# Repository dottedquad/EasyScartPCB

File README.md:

# EasyScartPCB
A simplified SCART cable PCB optimized for US modded TVs and hand soldering

### Summary
This is a fork of [screwbreaker/ScartPCB](https://github.com/screwbreaker/ScartPCB) designed for SCART modding on US-market TVs. Since these TVs don't use the +12V auto-switch or aspect ratio signal (SCART pin 8), this design removes the unnecessary boost converter and optimizes for easier hand assembly and part sourcing.

### Key Improvements
- **Hand-solder friendly**: All 0805 components (no tiny 0402 parts)
- **Better component sourcing**: Single package "B" tantalum 220µF/6.3V for decoupling instead of multiple MLCCs
- **Simplified buffer**: Single 74LVC1G17 instead of two transistors
- **Complete grounding**: All SCART ground signals properly connected
- **Removes unnecessary boost converter**: US TVs don't need the +12V signal

### How It Works
The PCB is modular – use 0Ω resistors as jumpers to enable/disable signals as needed:

**CSYNC Buffer**: The 74LVC1G17 buffer is specifically for Genesis/Mega Drive systems. Genesis outputs a TTL-level CSYNC that loses voltage when loaded by the 470Ω series resistor and 75Ω termination resistor. The buffer maintains +5V for proper sync detection. Close the NOBUF jumper to bypass if not needed.

**RGB Signals**: Use 0Ω resistors to pass through or add 75Ω termination resistors as needed.

**Jumpers**: NOBUF (bypass CSYNC buffer), MONO (mix left/right audio), RGB (enable blanking signal).

### PCB Details
4-layer board designed to fit inside standard SCART connectors. All components are 0805 or larger for easy hand soldering.

### 3D-Printed Cable Gland
SCART connector cable glands are notoriously brittle, so this project includes a 3D-printed replacement that's more durable.

### License
The PCBs are under the CERN OHL license. This is an open project – improvements and contributions are welcome.

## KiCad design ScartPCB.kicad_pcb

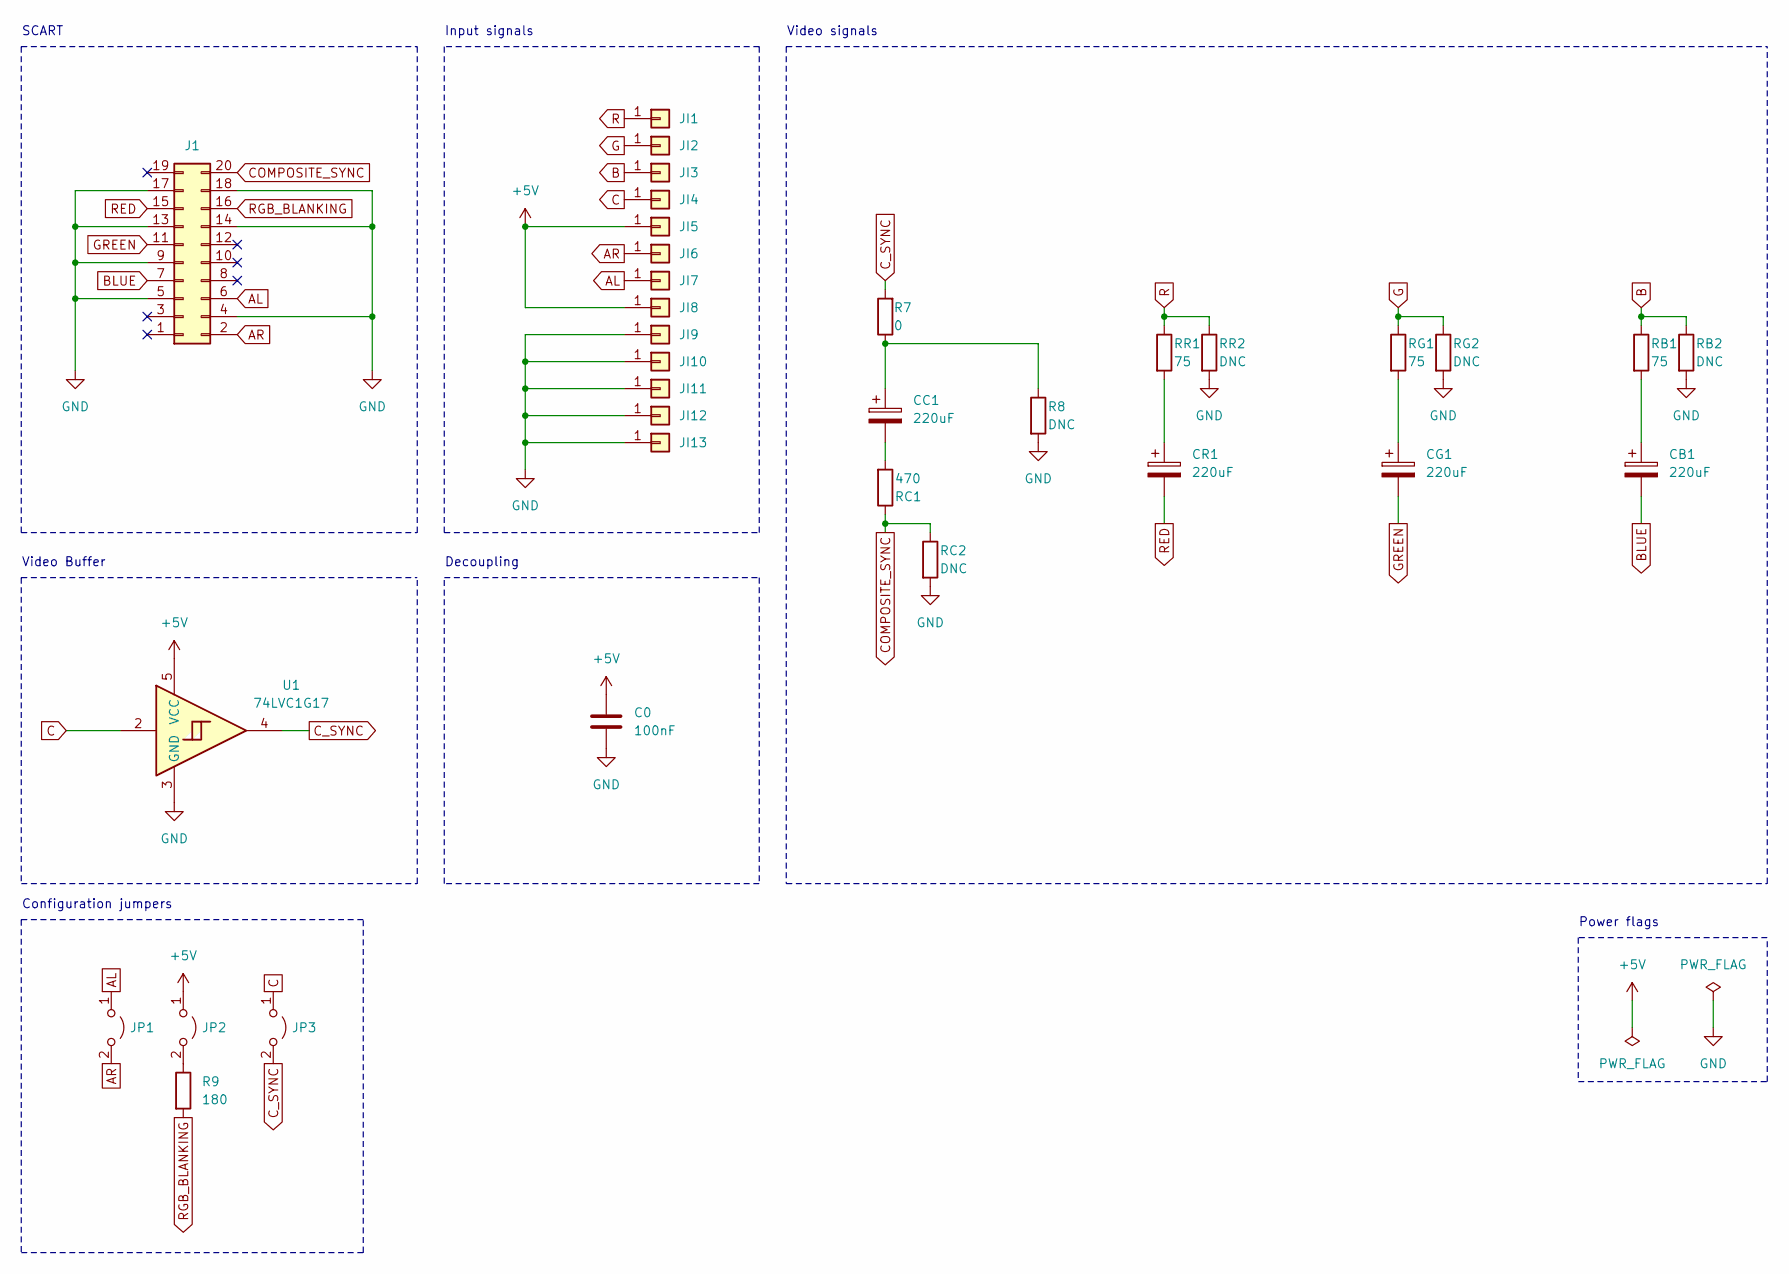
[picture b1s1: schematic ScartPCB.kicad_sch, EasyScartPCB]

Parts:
C0: 100nF; C_0805_2012Metric_Pad1.18x1.45mm_HandSolder
CB1: 220uF; CP_EIA-3528-21_Kemet-B_HandSolder
CC1: 220uF; CP_EIA-3528-21_Kemet-B_HandSolder
CG1: 220uF; CP_EIA-3528-21_Kemet-B_HandSolder
CR1: 220uF; CP_EIA-3528-21_Kemet-B_HandSolder
J1: Conn_02x10_Odd_Even; SCART
JI1, JI2, JI3, JI4, JI5, JI6, JI7, JI8, JI9, JI10, JI11, JI12: Conn_01x01; PAD2x2
JI13: Conn_01x01; PAD1.5x1.5
JP1, JP2, JP3: Jumper_2_Open; SolderJumper-2_P1.3mm_Open_TrianglePad1.0x1.5mm
R7: 0; R_0805_2012Metric_Pad1.20x1.40mm_HandSolder
R8: DNC; R_0805_2012Metric_Pad1.20x1.40mm_HandSolder
R9: 180; R_0805_2012Metric_Pad1.20x1.40mm_HandSolder
RB1: 75; R_0805_2012Metric_Pad1.20x1.40mm_HandSolder
RB2: DNC; R_0805_2012Metric_Pad1.20x1.40mm_HandSolder
RC1: 470; R_0805_2012Metric_Pad1.20x1.40mm_HandSolder; Manufacturer_Part_Number RC0402JR-07300RL
RC2: DNC; R_0805_2012Metric_Pad1.20x1.40mm_HandSolder
RG1: 75; R_0805_2012Metric_Pad1.20x1.40mm_HandSolder
RG2: DNC; R_0805_2012Metric_Pad1.20x1.40mm_HandSolder
RR1: 75; R_0805_2012Metric_Pad1.20x1.40mm_HandSolder
RR2: DNC; R_0805_2012Metric_Pad1.20x1.40mm_HandSolder
U1: 74LVC1G17; SC-74A-5_1.55x2.9mm_P0.95mm

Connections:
+5V: C0.1, JI5.1, JI8.1, JP2.1 (A), U1.5 (VCC)
AL: J1.6, JI7.1, JP1.1 (A)
AR: J1.2, JI6.1, JP1.2 (B)
B: JI3.1, RB1.1, RB2.1
BLUE: CB1.2, J1.7
C: JI4.1, JP3.1 (A), U1.2
COMPOSITE_SYNC: J1.20, RC1.1, RC2.1
C_SYNC: JP3.2 (B), R7.2, U1.4
G: JI2.1, RG1.1, RG2.1
GND: C0.2, J1.4, J1.5, J1.9, J1.13, J1.14, J1.17, J1.18, JI9.1, JI10.1, JI11.1, JI12.1, JI13.1, R8.2, RB2.2, RC2.2, RG2.2, RR2.2, U1.3 (GND)
GREEN: CG1.2, J1.11
unnamed: CB1.1, RB1.2
unnamed: CC1.1, R7.1, R8.1
unnamed: CC1.2, RC1.2
unnamed: CG1.1, RG1.2
unnamed: CR1.1, RR1.2
unnamed: JP2.2 (B), R9.1
R: JI1.1, RR1.1, RR2.1
RED: CR1.2, J1.15
RGB_BLANKING: J1.16, R9.2

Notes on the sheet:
Configuration jumpers
Power flags
Decoupling
Video Buffer
SCART
Input signals
Video signals

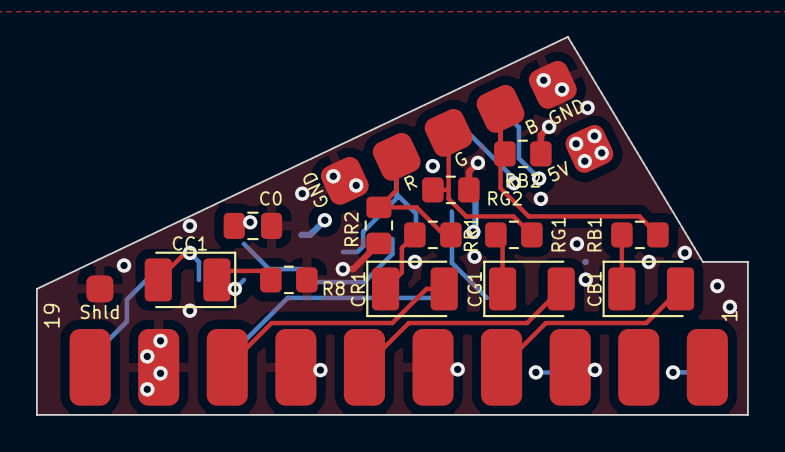
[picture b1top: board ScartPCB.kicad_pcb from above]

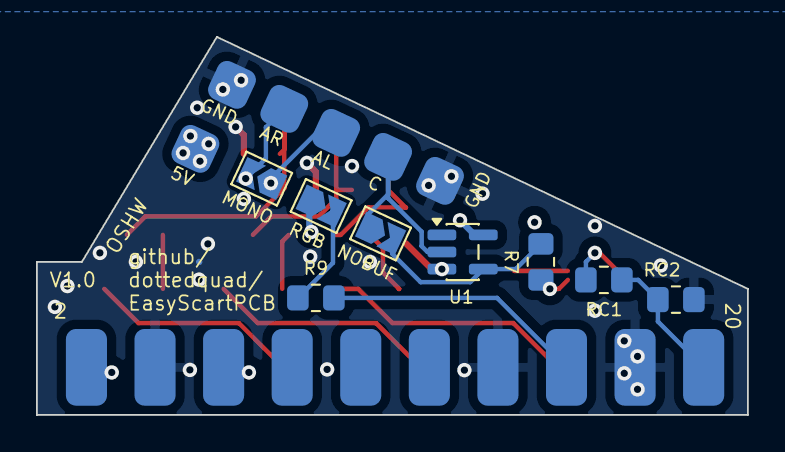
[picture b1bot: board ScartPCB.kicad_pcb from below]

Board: 4 copper layers, 39.5 x 21.0 mm, 34 parts (14 on the bottom side), 20 nets.

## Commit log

2026-03-17 Change it to work more like I want it to
2026-03-18 tweak position of csync cap
2026-03-18 Get ready for first run
